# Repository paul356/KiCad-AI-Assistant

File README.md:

# KiCad AI Assistant

KiCad AI Assistant is a KiCad action plugin that embeds an LLM-powered chat panel directly inside KiCad. It runs a built-in [MCP](https://modelcontextprotocol.io/) server and exposes a rich set of tools so the LLM can read and edit your schematics and PCB layouts through natural-language conversation.

Tested on **KiCad 10.0 / Linux & Windows**.

**Contributions welcome!** Bug reports, feature ideas, and pull requests are all appreciated — see [Contributing](#contributing) for how to get started.

## Table of Contents

- [KiCad AI Assistant](#kicad-ai-assistant)
  - [Table of Contents](#table-of-contents)
  - [Prerequisites](#prerequisites)
  - [Installation](#installation)
    - [1. Clone the repository (optional)](#1-clone-the-repository-optional)
    - [2. Install the plugin](#2-install-the-plugin)
    - [3. Create the plugin virtual environment](#3-create-the-plugin-virtual-environment)
    - [4. Load the plugin in KiCad](#4-load-the-plugin-in-kicad)
  - [Configuration](#configuration)
  - [Standalone MCP Server](#standalone-mcp-server)
  - [Feature Highlights](#feature-highlights)
  - [Available Tools](#available-tools)
    - [Project Tools](#project-tools)
    - [Symbol Library](#symbol-library)
    - [Schematic Editing](#schematic-editing)
    - [Schematic Groups](#schematic-groups)
    - [Schematic Analysis](#schematic-analysis)
    - [Hierarchical Sheets](#hierarchical-sheets)
    - [PCB Library](#pcb-library)
    - [PCB Query](#pcb-query)
    - [PCB Editing](#pcb-editing)
    - [PCB Routing](#pcb-routing)
    - [PCB Placement](#pcb-placement)
    - [PCB Groups](#pcb-groups)
    - [PCB Zones](#pcb-zones)
    - [DRC \& Design Rules](#drc--design-rules)
    - [Versioning \& Export](#versioning--export)
    - [Skill System](#skill-system)
    - [KiCad IPC](#kicad-ipc)
  - [Project Structure](#project-structure)
  - [Troubleshooting](#troubleshooting)
  - [Contributing](#contributing)
  - [License](#license)

## Prerequisites

- KiCad 10.0 or higher
- [`uv`](https://github.com/astral-sh/uv) — manages the Python virtual environment and installs the correct Python version automatically
  - Linux/macOS: `curl -Lsf https://astral.sh/uv/install.sh | sh`
  - Windows: `powershell -ExecutionPolicy ByPass -c "irm https://astral.sh/uv/install.ps1 | iex"`
- An API key for OpenAI, Anthropic, Amazon Bedrock, or a compatible LLM provider (Ollama needs none)

## Installation

### 1. Clone the repository (optional)

Only needed if you want to build the plugin from source or contribute to the project. Skip this step if you're downloading the pre-built plugin from the Releases page.

```bash
git clone https://github.com/paul356/KiCad-AI-Assistant.git
cd KiCad-AI-Assistant
```

### 2. Install the plugin

Two release archives are published:

- `kicad_ai_assistant.zip` — manual installation and the in-panel updater.
- `kicad_ai_assistant_pcm.zip` — installation through KiCad's Plugin and Content Manager ("Install from File…").

Both install the same plugin contents; the installed folder names differ (`kicad_ai_assistant/` for manual installs, `com_github_paul356_kicad-ai-assistant/` for PCM). `10.0` below is your KiCad `<major>.<minor>` version. `KICAD_DOCUMENTS_HOME` overrides the documents directory on every OS.

| OS | Manual install: `scripting/plugins` | PCM install: `3rdparty/plugins` |
|----|-------------------------------------|---------------------------------|
| Linux | `~/.local/share/kicad/10.0/scripting/plugins` | `~/.local/share/kicad/10.0/3rdparty/plugins` |
| macOS | `~/Documents/KiCad/10.0/scripting/plugins` | `~/Documents/KiCad/10.0/3rdparty/plugins` |
| Windows | `%USERPROFILE%\Documents\KiCad\10.0\scripting\plugins` | `%USERPROFILE%\Documents\KiCad\10.0\3rdparty\plugins` |

Download `kicad_ai_assistant.zip` from the [Releases page](https://github.com/paul356/KiCad-AI-Assistant/releases) and unzip it into the manual directory:

**Linux:**
```bash
KICAD_PLUGIN_DIR=~/.local/share/kicad/10.0/scripting/plugins
mkdir -p "$KICAD_PLUGIN_DIR"
unzip kicad_ai_assistant.zip -d "$KICAD_PLUGIN_DIR"
```

**macOS:**
```bash
KICAD_PLUGIN_DIR=~/Documents/KiCad/10.0/scripting/plugins
mkdir -p "$KICAD_PLUGIN_DIR"
unzip kicad_ai_assistant.zip -d "$KICAD_PLUGIN_DIR"
```

**Windows (PowerShell):**
```powershell
$KICAD_PLUGIN_DIR = "$env:USERPROFILE\Documents\KiCad\10.0\scripting\plugins"
New-Item -ItemType Directory -Force -Path $KICAD_PLUGIN_DIR
Expand-Archive -Path kicad_ai_assistant.zip -DestinationPath $KICAD_PLUGIN_DIR
```

The archive already contains the `kicad_ai_assistant/` root directory. Keep that name so the documented `cd`/setup commands and the manual-install convention match; renaming the installed folder is unsupported. Do not hand-unzip this archive into `3rdparty/plugins` — that directory belongs to the Plugin and Content Manager, and a manually copied folder there is not a PCM install.

**Plugin and Content Manager:** open **Preferences → Plugin and Content Manager → Install from File…** and select `kicad_ai_assistant_pcm.zip`. KiCad extracts the package to `<3rdparty>/plugins/com_github_paul356_kicad-ai-assistant/`; that package directory is the plugin directory (its `__init__.py` sits directly inside it). Do not unzip this archive yourself. PCM updates keep `.venv` and the freerouting JAR (`keep_on_update`); rerun the setup script after an update so the venv gets the matching `kcaa` version.

Or build from source:

```bash
# In the repo root:
make dist-plugin          # dist/kicad_ai_assistant.zip (manual install + updater)
make dist-pcm             # dist/kicad_ai_assistant_pcm.zip (PCM install)

# Linux:
KICAD_PLUGIN_DIR=~/.local/share/kicad/10.0/scripting/plugins
mkdir -p "$KICAD_PLUGIN_DIR"
unzip dist/kicad_ai_assistant.zip -d "$KICAD_PLUGIN_DIR"

# macOS:
KICAD_PLUGIN_DIR=~/Documents/KiCad/10.0/scripting/plugins
mkdir -p "$KICAD_PLUGIN_DIR"
unzip dist/kicad_ai_assistant.zip -d "$KICAD_PLUGIN_DIR"
```

### 3. Create the plugin virtual environment

Run the setup script from inside the installed plugin directory to create a `.venv`, install `kcaa` from PyPI, install **PyMuPDF** (imported as `fitz`, used for PDF import), and download the freerouting JAR. This requires `uv`; when it is missing the script prints an error and exits non-zero — install it from <https://docs.astral.sh/uv/getting-started/installation/> or with the command in [Prerequisites](#prerequisites). `uv` will automatically install the required Python version.

**Linux:**
```bash
cd ~/.local/share/kicad/10.0/scripting/plugins/kicad_ai_assistant
./setup_plugin.sh
```

**macOS:**
```bash
cd ~/Documents/KiCad/10.0/scripting/plugins/kicad_ai_assistant
./setup_plugin.sh
```

**Windows (PowerShell):**
```powershell
cd "$env:USERPROFILE\Documents\KiCad\10.0\scripting\plugins\kicad_ai_assistant"
.\setup_plugin.ps1
```

**Windows (Command Prompt):**
```cmd
cd /d "%USERPROFILE%\Documents\KiCad\10.0\scripting\plugins\kicad_ai_assistant"
setup_plugin.bat
```

For a PCM install, run the same script from `...\3rdparty\plugins\com_github_paul356_kicad-ai-assistant`. The script detects your KiCad version from the plugin directory path. KiCad already provides all necessary environment variables (`KICAD_VERSION`, `KICAD*_DIR`, etc.), so no `.env` file is needed.

The short version of these instructions also ships inside the plugin zip (`kicad_plugin/README.md`).

### 4. Load the plugin in KiCad

1. Open KiCad and load your project.
2. Open the **PCB Editor**.
3. Go to **Preferences → Plugins** and enable **Enable KiCad API**. The panel needs this IPC socket for **Reload PCB** and the `update_pcb_from_schematic` tool; without it those two fail, while file-based editing keeps working. This package does not declare the IPC runtime, so KiCad does not prompt for the toggle — enable it manually.
4. Go to **Tools → External Plugins → Refresh Plugins**.
5. Click **KiCad AI Assistant** in the plugin list to open the chat panel.
6. Go to **Options → Settings** and enter your LLM API key.

The panel publishes the open project from the PCB editor. Editing tools that
need a project (including the automatic pre-edit snapshots) therefore require
a saved KiCad project with the PCB editor open; when no project can be read
they return an actionable error instead of guessing from sibling files.
Save the project and open its PCB editor, then retry.

## Configuration

Plugin settings are stored in the KiCad user config directory:

Settings file: `~/.config/kicad/10.0/kcaa/kicad_ai_assistant.json`

All settings can be changed through **Options → Settings** in the plugin panel:

| Setting | Description | Default |
|---------|-------------|---------|
| `llm_provider` | LLM provider: `openai`, `anthropic`, `ollama`, or `bedrock` | `openai` |
| `llm_api_key` | Your LLM API key (stored with owner-only permissions). For `bedrock`, a Bedrock API key used as a bearer token | *(empty)* |
| `llm_model` | Model name. For `bedrock`, a Bedrock model or inference-profile id — newer Claude models need the cross-region profile form, e.g. `us.anthropic.claude-opus-5-5` (swap `us.` for your region) | `gpt-4o` |
| `llm_base_url` | Custom endpoint URL (overrides the provider default) | *(provider default)* |
| `llm_aws_region` | AWS region for the Bedrock endpoint (also used for SigV4 signing) | `us-east-1` |
| `llm_aws_access_key_id` | AWS access key id — set this (plus the secret) to use SigV4 instead of a Bedrock API key | *(empty)* |
| `llm_aws_secret_access_key` | AWS secret access key for SigV4 auth | *(empty)* |
| `llm_aws_session_token` | Optional STS session token for temporary AWS credentials | *(empty)* |
| `server_port` | Fixed port for the built-in MCP server (`0` = auto) | `0` |
| `mcp_tool_timeout_seconds` | Per-call deadline (s) for MCP tool calls (e.g. PCB routing); longer calls end the turn with an explicit timeout error. Takes effect after the plugin restarts | `300` |
| `show_tool_log` | Show tool-call log panel by default | `true` |
| `llm_context_tokens` | Total context window size in tokens | `128000` |
| `llm_compact_threshold` | Trigger context compaction at this usage fraction | `0.70` |

### Amazon Bedrock

Bedrock requests go to the native Bedrock Runtime `InvokeModel` API (not the OpenAI-compatible endpoint, which only serves non-Claude models), using the Anthropic Messages format. Authentication is chosen automatically:

- **Bedrock API key** — leave the AWS credential fields blank and put the key in `llm_api_key`; it is sent as a bearer token.
- **AWS SigV4** — set `llm_aws_access_key_id` + `llm_aws_secret_access_key` (and optionally `llm_aws_session_token`); requests are signed with SigV4 for the configured `llm_aws_region`.

Use a model id enabled in your account/region — the cross-region inference-profile ids work well, e.g. `us.anthropic.claude-opus-5-5` or a versioned id like `us.anthropic.claude-sonnet-4-5-20250929-v1:0`. List yours with `aws bedrock list-inference-profiles --region <region>`. Responses are streamed to the chat panel in a single block, since Bedrock's streaming uses a binary framing the plugin's transport does not decode.

## Standalone MCP Server

You can also run `kcaa` as a standalone MCP server without the KiCad plugin. This is useful for integrating with other MCP clients (e.g., Claude Desktop, Cursor).

Create a `.env` file in your working directory:

```dotenv
KICAD_SEARCH_PATHS=/home/user/pcb
KICAD_APP_PATH=/usr
KICAD_VERSION=10.0
KICAD_CONFIG_DIR=~/.config/kicad/10.0
KICAD_3RD_PARTY=~/.local/share/kicad/10.0/3rdparty
MCP_TRANSPORT=streamable-http
```

Then start the server:

```bash
kcaa
```

## Feature Highlights

- **Schematic editing** — Add/remove symbols, set/rename properties, draw and delete wires, connect pins automatically
- **Hierarchical sheets** — Create, read, update, and delete hierarchical sheet symbols and sheet pins
- **PCB footprint library** — Search the system footprint library index by name, description, or tag; set footprints on schematic symbols
- **PCB synchronisation** — Trigger *Update PCB from Schematic* via KiCad's IPC API
- **PCB placement** — Query, move, rotate, flip, align, and distribute footprints; define or clear the board outline
- **Design rules** — View and modify board-level design rules, net classes, and custom DRC rules
- **DRC** — Run design-rule checks directly from the plugin
- **Context management** — Automatic compaction of the LLM context window when it approaches the limit
- **Session management** — Save, restore, and reset the current conversation; save design snapshots for rollback
- **Skill system** — On-demand workflow guidance for the LLM via user-definable Markdown skill files

## Available Tools

**Naming convention** — a `library_` prefix means a **definition inside a library**; no prefix means an **object placed on a board or in a schematic**. A `library_` tool never returns placement.

- `get_library_footprint` — footprint **definition** in a library; key `library_name` + `footprint_name`. Returns pads/courtyard/attributes; pad coordinates are footprint-local, with no board-level placement anchor.
- `get_footprint` — footprint **placed on a PCB**; key `pcb_path` + `references[]` (world position, rotation, layer, properties, pads).
- `list_symbol_properties` — symbol **placed in a schematic**; key `schematic_path` + `references[]` (properties only, no geometry, position, or nets).
- `extract_schematic_netlist` — returns the **whole netlist**, including the placement of **every** placed symbol (`components[ref].units[n].position`, `rotation`, per-unit `body_bbox`, world-coordinate `pins`); not a cheap single-coordinate lookup.
- `find_component_connections` — placement and connections for a **single reference** (`project_path` + `component_ref`); returns only that reference's `component_info` (also with `units[n].position`), not the whole netlist.

### Project Tools

| Tool | Description |
|------|-------------|
| `list_projects` | Find and list all KiCad projects |
| `get_project_structure` | Get the structure and files of a KiCad project |
| `open_project` | Open a KiCad project in KiCad |

### Symbol Library

| Tool | Description |
|------|-------------|
| `sync_symbol_index` | Build or refresh the symbol library index |
| `get_symbol_sync_status` | Query symbol index build progress |
| `get_symbol_index_stats` | Get statistics about the symbol index |
| `list_symbol_libraries` | List all symbol libraries; `list_library_symbols` lists the symbols inside one library (keyed by `library_name`) |
| `search_library_symbols` | Full-text search across indexed symbols |
| `get_library_symbol` | Look up a symbol by library and name |
| `list_library_symbols` | List the symbols inside one library, keyed by `library_name`; `list_symbol_libraries` lists all libraries |
| `get_library_symbol_pins` | Get pin definitions for a symbol |
| `create_symbol_library` | Create a new `.kicad_sym` library (global 3rd-party or project-local) and register it in the library table |
| `delete_symbol_library` | Delete an empty symbol library (file, library-table entry, and index) |
| `add_symbols_to_library` | Copy symbols from a schematic's cached `lib_symbols` into an existing library |
| `remove_symbols_from_library` | Remove named symbol definitions from a library and re-index it |
| `update_library_symbol_pin` | Rename a pin number and/or pin name in a library symbol definition (format-preserving) |
| `find_symbols_not_in_libraries` | List schematic symbols that resolve to no available library (read-only) |

### Schematic Editing

| Tool | Description |
|------|-------------|
| `add_symbol_to_schematic` | Place a symbol on the schematic |
| `create_symbol` | Define a new symbol into a symbol library (definition only — no schematic placement) |
| `place_symbol_relative` | Place a symbol relative to an existing component |
| `remove_symbol_from_schematic` | Remove placed symbol by reference |
| `move_component` | Move and/or rotate a placed component |
| `set_symbol_property` | Set a property field on a placed symbol |
| `update_schematic_symbol_pin` | Rename a pin number and/or pin name in a schematic's cached `lib_symbols` copy |
| `update_schematic_symbol_from_library` | Refresh a schematic's cached `lib_symbols` definition from the library (graphics, pins, unit sub-symbols and definition properties; placements keep their fields) |
| `rename_symbol` | Rename a placed symbol's reference designator |
| `list_symbol_properties` | List properties (name → value) of placed schematic symbols — no geometry, position, or nets |
| `delete_symbol_property` | Delete a property from a placed symbol |
| `check_reference_conflicts` | Check for duplicate reference designators |
| `connect_points_with_wire` | Route a smart orthogonal wire between two points |
| `connect_pins_with_wire` | Connect two symbol pins with a wire |
| `delete_wire_from_schematic` | Remove wire segments by endpoints |
| `add_label_to_schematic` | Add a local net label |
| `list_labels_in_schematic` | List all local net labels |
| `delete_label_from_schematic` | Delete net labels |
| `add_no_connect` | Add a no-connect flag at a pin coordinate |
| `list_no_connects` | List all no-connect flags |
| `remove_no_connect` | Remove no-connect flag(s) by coordinate |
| `get_schematic_sheet_info` | Get drawing area, paper size, and grid |
| `find_free_area` | Find candidate areas for placing a block |

### Schematic Groups

| Tool | Description |
|------|-------------|
| `assign_symbols_to_group` | Assign symbols to a named placement group (stored as the `placement_group` property) |
| `list_symbol_groups` | List all symbol placement groups with member counts and bounding boxes |
| `get_symbol_group` | Get a group's members, positions, anchor and bounding box |
| `score_symbol_group` | Score intra-group spacing (mean nearest-neighbour distance and spread) |
| `place_symbol_group` | Arrange a group in a grid around its anchor and drop it in a free sheet area |
| `move_symbol_group` | Translate a whole group to a new anchor position, keeping its internal layout |
| `rotate_symbol_group` | Rotate a whole group rigidly around its anchor (counter-clockwise positive) |

### Schematic Analysis

| Tool | Description |
|------|-------------|
| `extract_schematic_netlist` | Extract netlist from a schematic |
| `find_component_connections` | Find all connections for a component |
| `run_erc` | Run Electrical Rules Check (headless `kicad-cli`) and return violations |
| `identify_circuit_patterns` | Identify common circuit patterns |
| `validate_project` | Basic validation of a KiCad project |

### Hierarchical Sheets

| Tool | Description |
|------|-------------|
| `list_sheet_symbols` | List all hierarchical sheet symbols in a schematic |
| `get_sheet_hierarchy` | Get the full sheet hierarchy tree |
| `add_sheet_symbol` | Add a new hierarchical sheet symbol |
| `remove_sheet_symbol` | Remove a sheet symbol (with optional child file deletion) |
| `update_sheet_symbol` | Update a sheet symbol's properties and geometry |
| `add_sheet_pin` | Add a hierarchical pin to a sheet symbol |
| `remove_sheet_pin` | Remove a hierarchical pin from a sheet symbol |

### PCB Library

| Tool | Description |
|------|-------------|
| `sync_footprint_index` | Build or refresh the footprint library index |
| `get_footprint_sync_status` | Query footprint index build progress |
| `list_footprint_libraries` | List all available footprint libraries |
| `search_library_footprints` | Search footprints by name, description, or tag |
| `get_library_footprint` | Get a footprint **library definition** (pads, bounding box, etc.) by library name + footprint name — not a board placement |
| `list_library_footprints` | List every footprint in one library (names and light metadata) (offset paging) |
| `find_footprints_not_in_libraries` | List board footprints missing from every indexed library |
| `create_footprint_library` | Create a global 3rdparty or project-local footprint library |
| `add_footprints_to_library` | Export explicitly named board footprints into a library |
| `delete_footprint_library` | Delete an empty footprint library (directory, library-table entry, and index) |
| `remove_footprints_from_library` | Remove named footprints from a footprint library and re-index it |

### PCB Query

| Tool | Description |
|------|-------------|
| `get_board_info` | Get basic PCB board information |
| `list_footprints` | List all footprints placed on the board |
| `get_footprint` | Get details of footprints **placed on the PCB**, one payload per reference in `references` (pads, properties, Edge.Cuts geometry) |
| `get_footprint_bbox` | Get the courtyard bounding box of a footprint |
| `get_board_bounding_box` | Get the union bounding box of all footprints |
| `list_nets` | List all nets on the board |
| `list_tracks` | List track segments and arcs grouped into traces, optionally filtered by net and layer |
| `list_vias` | List through-hole vias with position, size, drill, layers and net, optionally filtered by net |
| `get_ratsnest` | Get unrouted ratsnest connections |
| `score_placement` | Score the current PCB placement quality |
| `suggest_placement_order` | Get recommended footprint placement order |

### PCB Editing

| Tool | Description |
|------|-------------|
| `get_board_outline` | Read Edge.Cuts board outline elements |
| `clear_board_outline` | Clear the board outline |
| `add_board_outline_segment` | Add a line segment to the board outline |
| `add_board_outline_arc` | Add an arc to the board outline |
| `set_board_outline_rect` | Set a rectangular board outline (with optional rounded corners) |
| `set_footprint_property` | Set a property field on a footprint |
| `add_footprints_to_pcb` | Import footprints from footprint libraries onto the board at given positions, assigning every pad's net |
| `remove_footprints_from_pcb` | Remove footprints from the board by reference designator (batch) |
| `update_pcb_from_schematic` | Trigger *Update PCB from Schematic* via KiCad IPC |

### PCB Routing

| Tool | Description |
|------|-------------|
| `pcb_route_pad_to_pad` | Route a single track between two pads with the obstacle-avoiding router (PNS shove or grid A*), optionally across layers via through-vias |
| `pcb_add_vias` | Add one or more through-hole vias in a single write, pre-checked against netclass and clearance rules |
| `pcb_delete_tracks` | Delete track segments and arcs matched by their endpoint coordinates |
| `pcb_delete_vias` | Delete vias matched by their (x, y) position |

### PCB Placement

| Tool | Description |
|------|-------------|
| `set_footprint_position` | Move and/or rotate one or more footprints (via `items`) |
| `flip_footprint` | Flip a footprint between top and bottom layer |
| `align_footprints` | Align footprints to the same axis |
| `distribute_footprints` | Distribute footprints evenly along an axis |
| `move_footprints_by_delta` | Translate footprints by (dx, dy) |
| `find_free_pcb_area` | Find an area free of existing footprints |

### PCB Groups

| Tool | Description |
|------|-------------|
| `assign_footprints_to_group` | Assign footprints to a placement group |
| `list_footprint_groups` | List all placement groups on the board |
| `get_footprint_group` | Get details of a placement group |
| `score_footprint_group` | Score intra-group placement quality |
| `place_footprint_group` | Place all members of a group |
| `move_footprint_group` | Translate a placed group |
| `rotate_footprint_group` | Rotate a placed group around its anchor |

### PCB Zones

| Tool | Description |
|------|-------------|
| `list_zones` | List all copper-pour and keepout zones |
| `add_zone` | Add a copper-pour or keepout zone |
| `delete_zone` | Delete a zone by UUID |
| `refill_zones` | Refill all zones on the PCB |

### DRC & Design Rules

| Tool | Description |
|------|-------------|
| `get_effective_design_rules` | Get all design constraints (board rules, net classes, custom rules) |
| `set_design_rules` | Update board-level design rule minimums |
| `set_net_class_rules` | Create or update a net class's design parameters |
| `assign_nets_to_class` | Assign nets to a net class |
| `remove_nets_from_class` | Remove nets from a net class (revert to Default) |
| `delete_net_class` | Delete a net class |
| `add_custom_rule` | Add a custom DRC rule to the project |
| `del_custom_rule` | Delete a custom DRC rule by name |
| `run_drc_check` | Open the KiCad DRC dialog |
| `analyze_bom` | Analyze the bill of materials |
| `export_bom_csv` | Export the BOM to CSV |

### Versioning & Export

| Tool | Description |
|------|-------------|
| `save_project_version` | Save a project version archive (schematic+PCB+project file) |
| `list_project_versions` | List saved project version archives |
| `restore_project_version` | Restore project files together to a saved archive |
| `generate_pcb_thumbnail` | Render a PCB thumbnail image |
| `export_pcb_layer_image` | Render the board — or a single copper layer — as an image returned to the model; writes a PNG file only when `output_dir` is given |

### Skill System

| Tool | Description |
|------|-------------|
| `list_skills` | List all available skill documents |
| `get_skill` | Get the full content of a skill document |
| `add_skill` | Create a new skill document |
| `append_to_skill` | Append content to an existing skill |
| `delete_skill` | Soft-delete a skill document |

### KiCad IPC

| Tool | Description |
|------|-------------|
| `check_kicad_ipc_connection` | Check if the KiCad IPC socket is responsive |
| `save_document` | Save the active document in KiCad |
| `reload_kicad` | Reload documents in the running KiCad editor |

## Project Structure

```
kcaa/
├── main.py                  # MCP server entry point
├── pyproject.toml           # Package metadata and dependencies
├── run_tests.py             # Test runner script
├── kcaa/                    # MCP server package
│   ├── server.py            # Server setup and tool registration
│   ├── config.py            # Configuration and KiCad path detection
│   ├── context.py           # Request context management
│   ├── tools/               # All MCP tool implementations
│   ├── resources/           # MCP resource handlers
│   ├── prompts/             # MCP prompt templates
│   └── utils/               # Utility functions
├── kicad_plugin/            # KiCad action plugin
│   ├── __init__.py          # Plugin entry point (KiCadAIPlugin)
│   ├── server_manager.py    # Start/stop the kcaa subprocess
│   ├── llm_client.py        # Agentic tool-call loop (OpenAI / Anthropic)
│   ├── context_bridge.py    # Collect active project paths from KiCad
│   ├── settings.py          # Load/save plugin settings
│   ├── autorouter.py        # FreeRouting integration
│   ├── tool_registry.py     # Tool metadata and categorization
│   ├── setup_plugin.sh      # Linux/macOS setup script
│   ├── setup_plugin.ps1     # Windows PowerShell setup script
│   ├── setup_plugin.bat     # Windows batch setup script
│   └── ui/                  # wxPython chat panel and settings dialog
├── docs/                    # Feature documentation
└── tests/                   # Unit tests
```

## Troubleshooting

**Plugin does not appear in KiCad:**
- Manual install: confirm you used the documented folder name `<documents>/kicad/<ver>/scripting/plugins/kicad_ai_assistant` (the old instructions used `kicad_ai_plugin`) so the commands below work.
- PCM install: confirm `<documents>/kicad/<ver>/3rdparty/plugins/com_github_paul356_kicad-ai-assistant` exists and came from `kicad_ai_assistant_pcm.zip`.
- Run **Tools → External Plugins → Refresh Plugins** after installing.
- Linux: Check that `setup_plugin.sh` completed without errors and that `.venv/bin/python` exists inside the plugin directory.
- Windows: Check that `setup_plugin.bat` (or `setup_plugin.ps1`) completed without errors and that `.venv/Scripts/python.exe` exists inside the plugin directory.
- If the setup script failed, see [the setup troubleshooting entry](docs/troubleshooting.md#setup-script-fails-and-the-window-closes).

**MCP server fails to start:**
- Linux: Check the plugin log in `~/.config/kicad/` for Python tracebacks.
- Windows: Check the plugin log in `%APPDATA%/kicad/` for Python tracebacks.

**Schematic editor does not refresh after edits:**
- This is a current KiCad IPC limitation. Use **File → Reload** or press **Ctrl+Z / Ctrl+Y** to trigger a refresh in the schematic editor.

**LLM API errors:**
- Confirm the API key is correct in **Options → Settings**.
- Check that `llm_model` is a valid model name for your chosen provider.

## Contributing

1. Fork the repository
2. Create a feature branch
3. Add your changes with tests
4. Submit a pull request **against the `develop` branch**

> **PR requirements:**
> - One pull request should contain **only one** fix, enhancement, or
>   feature. If you have multiple independent changes, please submit them
>   as separate pull requests.
> - Include tests for your changes.

> **Branch policy:**
> - The `develop` branch is where new features are stabilized — please
>   submit your changes there first so they can be tested and reviewed.
> - The `main` branch is reserved for releasing versions. Changes are
>   merged from `develop` into `main` once they have passed testing.

## License

This project is open source under the MIT license.

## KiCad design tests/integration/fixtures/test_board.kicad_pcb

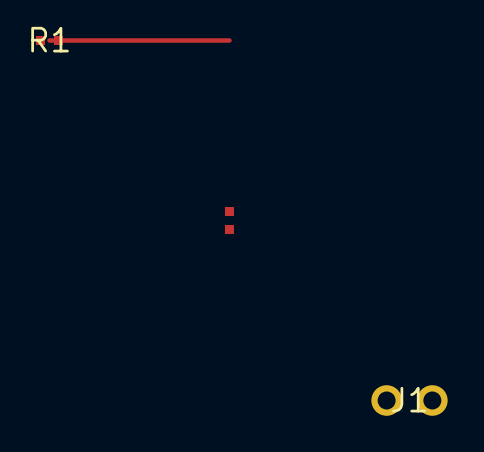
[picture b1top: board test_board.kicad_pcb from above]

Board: 2 copper layers, 3 parts (1 on the bottom side), 3 nets.

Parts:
C1: 100nF; C_0402_1005Metric
J1: Conn_01x02; PinHeader_1x02_P2.54mm_Vertical
R1: 10k; R_0402_1005Metric

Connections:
GND: J1.1, R1.2
NET_A: C1.2, J1.2
VCC: C1.1, R1.1

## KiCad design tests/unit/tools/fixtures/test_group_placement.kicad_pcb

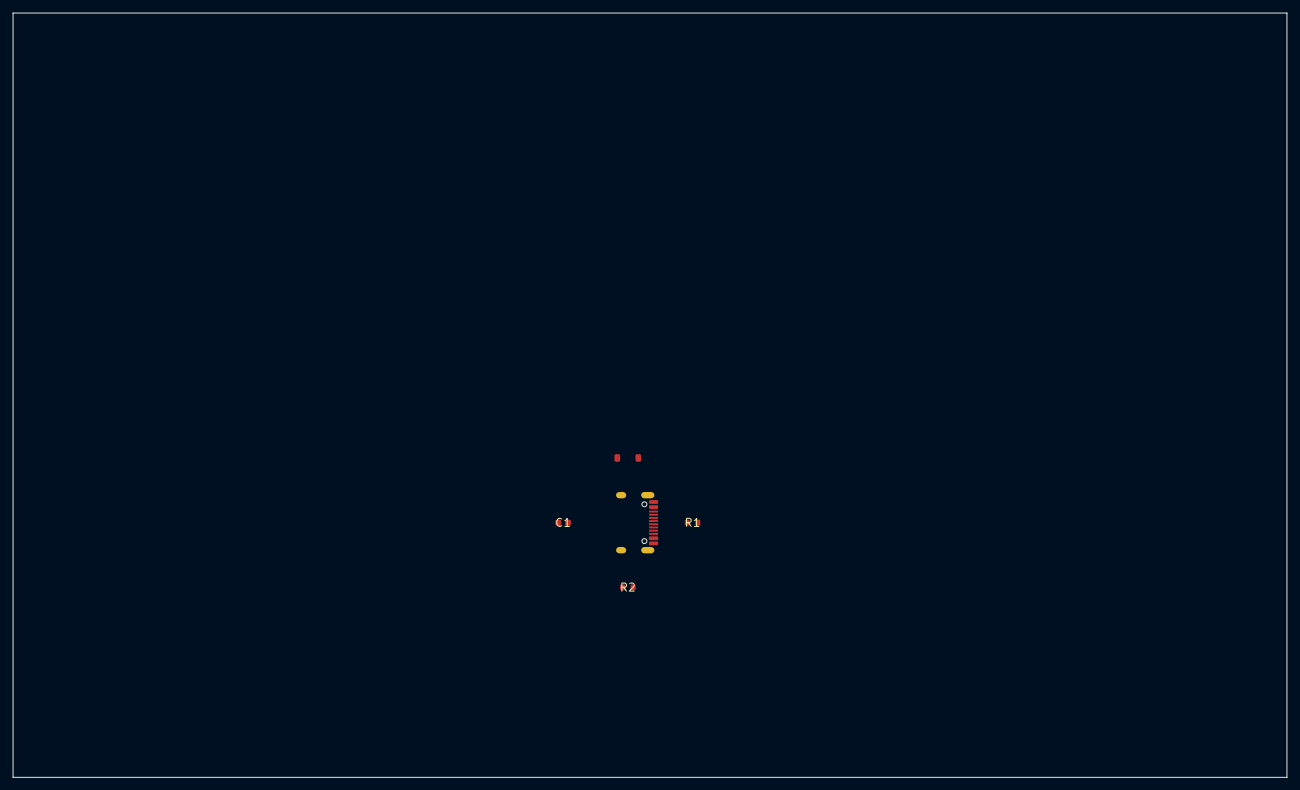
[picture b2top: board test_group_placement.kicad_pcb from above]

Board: 2 copper layers, 200.0 x 120.0 mm, 5 parts (0 on the bottom side), 6 nets, no tracks yet.

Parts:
C1: 100nF; C_0603_1608Metric
D1: B5819W; D_SOD-123
J3: USB_C_Receptacle_USB2.0_14P; USB_C_Receptacle_HRO_TYPE-C-31-M-12
R1, R2: 5.1k; R_0603_1608Metric

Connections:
GND: C1.2, J3.A1, J3.A12, J3.B1, J3.B12, J3.SH, R1.2, R2.1
unnamed: C1.1, D1.2, J3.A4, J3.A9, J3.B4, J3.B9
unnamed: J3.A5, R1.1
unnamed: J3.B5, R2.2
unnamed: J3.A6, J3.B6
unnamed: J3.A7, J3.B7
